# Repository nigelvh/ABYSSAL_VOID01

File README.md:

# ABYSSAL.NETWORK VOID01
A routing & switching learning platform built around the Raspberry Pi Compute Module 4, and the Microchip KSZ9477 gigabit ethernet switch.

## Hardware
These are the hardware design files. They're almost certainly terrible. Replicate this device at your own peril.

## Software
The Raspberry Pi Compute Module is installed with standard Raspbian. Configuration of the switching functions of the KSZ9477 are done via scripts communicating via the SPI bus. Configuration of routing functions are as per standard Linux methods.

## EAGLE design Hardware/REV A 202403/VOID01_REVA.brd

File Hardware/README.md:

# ABYSSAL.NETWORK VOID01 Hardware
This is a custom routing and switching learning platform based on the Raspberry Pi Compute Module 4 and the Microchip KSZ9477 gigabit ethernet switch.

The RPi provides for a standard linux platform to enable easy development, with simple scripting to configure the KSZ9477, and linux routing functions. This provides a lower barrier to entry learning platform, as compared to an embedded processor of some sort.

A CM4 Lite module is chosen, utilizing SD card based storage to simplify installation of the RPi OS.

A USB serial interface is provided to allow access to the RPi Serial Console, allowing for non-network based access/recovery.

The KSZ9477 switch is an inexpensive off-the-shelf switching chip, with a relatively rich feature set. Providing 5 PHY interfaces (4 ethernet jacks, and 1 connected to the onboard RPi), 1 RGMII interface (not used), and 1 SGMII interface (SFP Port).

A standard center-positive barrel jack accepts nominal 12V DC power. The input range should be roughly 8-26V. Onboard regulation generates 5V, 3.3V, 2.5V, and 1.2V rails necessary for the RPi and KSZ9477.

## REV A 202403
The first revision of the board. Designed in March 2024.

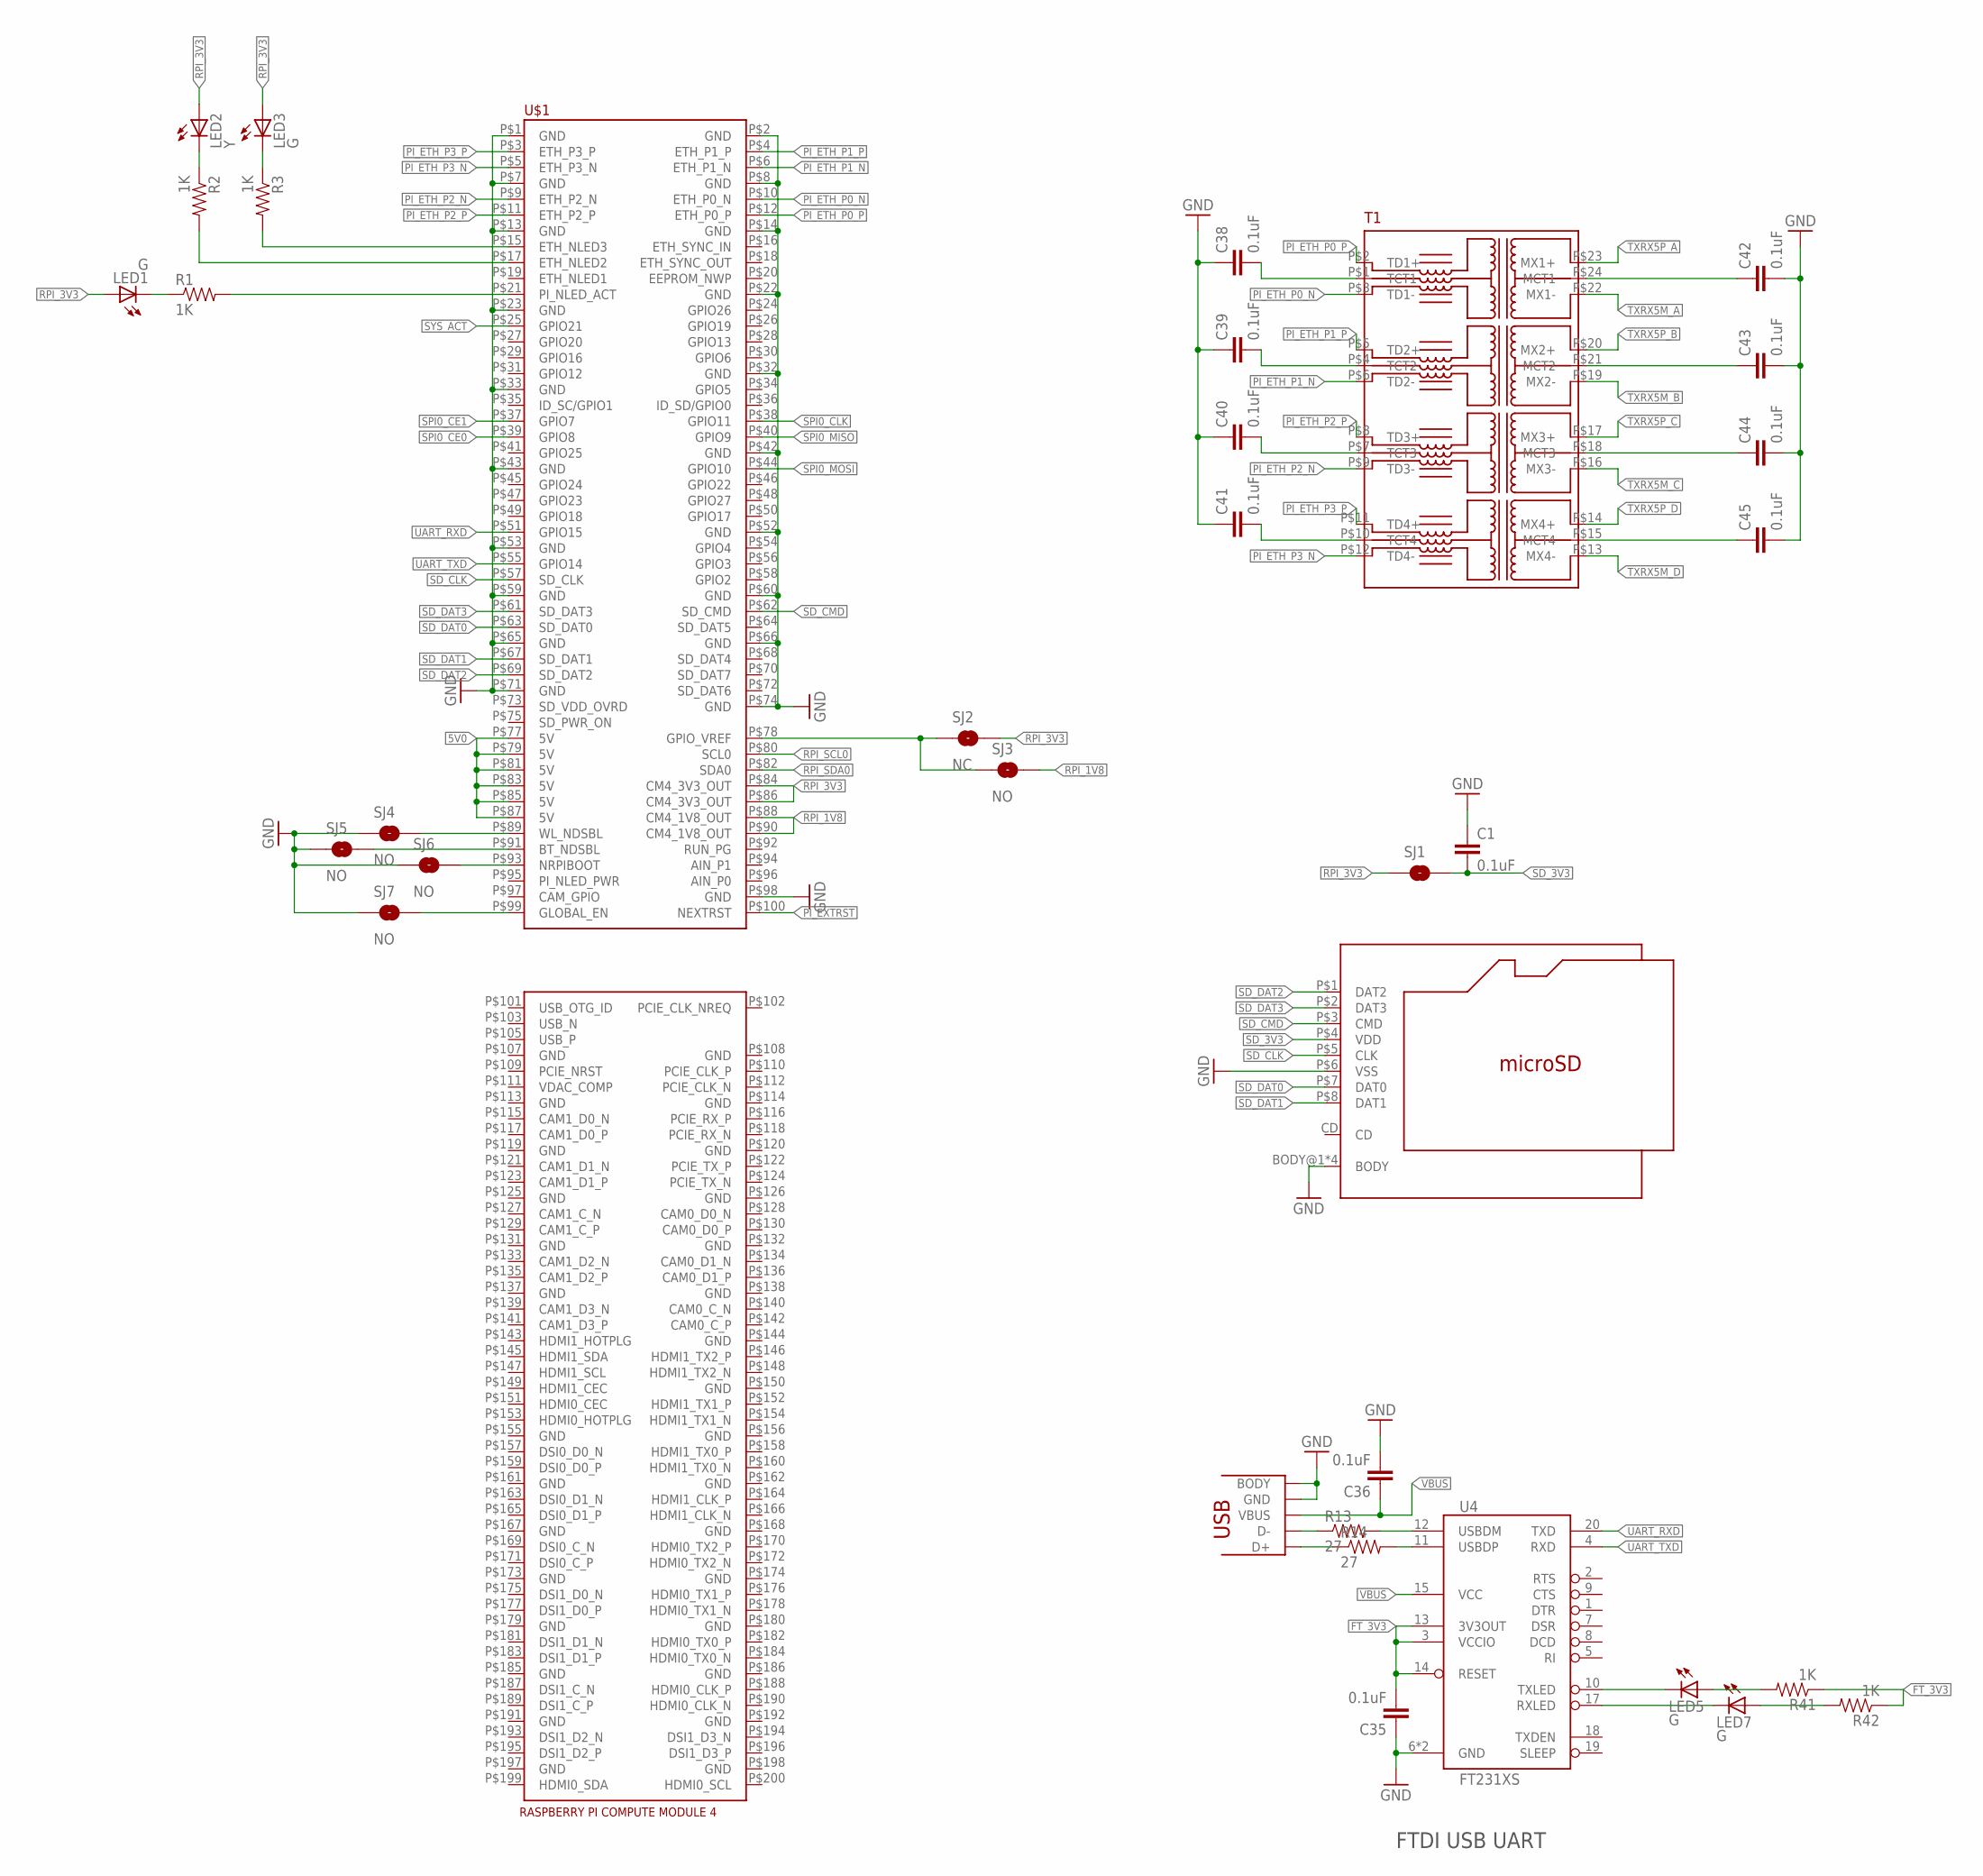
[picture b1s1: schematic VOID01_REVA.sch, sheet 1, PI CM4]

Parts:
C1, C35, C36, C38, C39, C40, C41, C42, C43, C44, C45: 0.1uF; 0603-CAP
J1: MICROSD; MSD-4-A
LED1, LED3, LED5, LED7: G; LED-0603
LED2: Y; LED-0603
R1, R2, R3: 1K; 0402-RES
R13, R14: 27; 0603-RES
R41, R42: 1K; 0603-RES
SJ1: SOLDERJUMPERTRACE; SJ_2S-TRACE
SJ2: NC; SJ_2S-TRACE
SJ3, SJ4, SJ5, SJ6, SJ7: NO; SJ_2S-NO
T1: HX6098NL
U4: FT231XS; SSOP-20
U$1: RPI-CM4
U$2: USB-MICROB; USB-MICROB-10118192

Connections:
5V0: U$1.P$77 (5V), U$1.P$79 (5V), U$1.P$81 (5V), U$1.P$83 (5V), U$1.P$85 (5V), U$1.P$87 (5V); also elsewhere on the board
FT_3V3: C35.2, R41.1, R42.1, U4.3 (VCCIO), U4.13 (3V3OUT), U4.14 (RESET)
GND: C1.1, C35.1, C36.2, C38.1, C39.1, C40.1, C41.1, C42.2, C43.2, C44.2, C45.2, J1.BODY@1 (BODY), J1.BODY@2 (BODY), J1.BODY@3 (BODY), J1.BODY@4 (BODY), J1.P$6 (VSS), SJ4.1, SJ5.1, SJ6.1, SJ7.1, U4.6 (GND), U4.16 (GND), U$1.P$1 (GND), U$1.P$2 (GND), U$1.P$7 (GND), U$1.P$8 (GND), U$1.P$13 (GND), U$1.P$14 (GND), U$1.P$22 (GND), U$1.P$23 (GND), U$1.P$32 (GND), U$1.P$33 (GND), U$1.P$42 (GND), U$1.P$43 (GND), U$1.P$52 (GND), U$1.P$53 (GND), U$1.P$59 (GND), U$1.P$60 (GND), U$1.P$65 (GND), U$1.P$66 (GND), U$1.P$71 (GND), U$1.P$74 (GND), U$1.P$98 (GND), U$2.5 (GND), U$2.BODY@1 (BODY), U$2.BODY@2 (BODY), U$2.BODY@3 (BODY), U$2.BODY@4 (BODY), U$2.BODY@5 (BODY), U$2.BODY@6 (BODY); also elsewhere on the board
unnamed: SJ2.1, SJ3.1, U$1.P$78 (GPIO_VREF)
unnamed: SJ4.2, U$1.P$89 (WL_NDSBL)
unnamed: SJ5.2, U$1.P$91 (BT_NDSBL)
unnamed: LED2.C, R2.1
unnamed: SJ6.2, U$1.P$93 (NRPIBOOT)
unnamed: R1.2, U$1.P$21 (PI_NLED_ACT)
unnamed: LED1.C, R1.1
unnamed: LED3.C, R3.1
unnamed: R2.2, U$1.P$17 (ETH_NLED2)
unnamed: R3.2, U$1.P$15 (ETH_NLED3)
unnamed: SJ7.2, U$1.P$99 (GLOBAL_EN)
unnamed: R13.1, U$2.2 (D-)
unnamed: R14.1, U$2.3 (D+)
unnamed: R14.2, U4.11 (USBDP)
unnamed: R13.2, U4.12 (USBDM)
unnamed: C38.2, T1.P$1 (TCT1)
unnamed: C39.2, T1.P$4 (TCT2)
unnamed: C40.2, T1.P$7 (TCT3)
unnamed: C41.2, T1.P$10 (TCT4)
unnamed: C45.1, T1.P$15 (MCT4)
unnamed: C44.1, T1.P$18 (MCT3)
unnamed: C43.1, T1.P$21 (MCT2)
unnamed: C42.1, T1.P$24 (MCT1)
unnamed: LED5.C, U4.10 (TXLED)
unnamed: LED5.A, R41.2
unnamed: LED7.C, U4.17 (RXLED)
unnamed: LED7.A, R42.2
PI_ETH_P0_N: T1.P$3 (TD1-), U$1.P$10 (ETH_P0_N)
PI_ETH_P0_P: T1.P$2 (TD1+), U$1.P$12 (ETH_P0_P)
PI_ETH_P1_N: T1.P$6 (TD2-), U$1.P$6 (ETH_P1_N)
PI_ETH_P1_P: T1.P$5 (TD2+), U$1.P$4 (ETH_P1_P)
PI_ETH_P2_N: T1.P$9 (TD3-), U$1.P$9 (ETH_P2_N)
PI_ETH_P2_P: T1.P$8 (TD3+), U$1.P$11 (ETH_P2_P)
PI_ETH_P3_N: T1.P$12 (TD4-), U$1.P$5 (ETH_P3_N)
PI_ETH_P3_P: T1.P$11 (TD4+), U$1.P$3 (ETH_P3_P)
PI_EXTRST: U$1.P$100 (NEXTRST); also elsewhere on the board
RPI_1V8: SJ3.2, U$1.P$88 (CM4_1V8_OUT), U$1.P$90 (CM4_1V8_OUT)
RPI_3V3: LED1.A, LED2.A, LED3.A, SJ1.1, SJ2.2, U$1.P$84 (CM4_3V3_OUT), U$1.P$86 (CM4_3V3_OUT)
RPI_SCL0: U$1.P$80 (SCL0); also elsewhere on the board
RPI_SDA0: U$1.P$82 (SDA0); also elsewhere on the board
SD_3V3: C1.2, J1.P$4 (VDD), SJ1.2
SD_CLK: J1.P$5 (CLK), U$1.P$57 (SD_CLK)
SD_CMD: J1.P$3 (CMD), U$1.P$62 (SD_CMD)
SD_DAT0: J1.P$7 (DAT0), U$1.P$63 (SD_DAT0)
SD_DAT1: J1.P$8 (DAT1), U$1.P$67 (SD_DAT1)
SD_DAT2: J1.P$1 (DAT2), U$1.P$69 (SD_DAT2)
SD_DAT3: J1.P$2 (DAT3), U$1.P$61 (SD_DAT3)
SPI0_CE0: U$1.P$39 (GPIO8); also elsewhere on the board
SPI0_CE1: U$1.P$37 (GPIO7)
SPI0_CLK: U$1.P$38 (GPIO11); also elsewhere on the board
SPI0_MISO: U$1.P$40 (GPIO9); also elsewhere on the board
SPI0_MOSI: U$1.P$44 (GPIO10); also elsewhere on the board
SYS_ACT: U$1.P$25 (GPIO21); also elsewhere on the board
TXRX5M_A: T1.P$22 (MX1-); also elsewhere on the board
TXRX5M_B: T1.P$19 (MX2-); also elsewhere on the board
TXRX5M_C: T1.P$16 (MX3-); also elsewhere on the board
TXRX5M_D: T1.P$13 (MX4-); also elsewhere on the board
TXRX5P_A: T1.P$23 (MX1+); also elsewhere on the board
TXRX5P_B: T1.P$20 (MX2+); also elsewhere on the board
TXRX5P_C: T1.P$17 (MX3+); also elsewhere on the board
TXRX5P_D: T1.P$14 (MX4+); also elsewhere on the board
UART_RXD: U4.20 (TXD), U$1.P$51 (GPIO15)
UART_TXD: U4.4 (RXD), U$1.P$55 (GPIO14)
VBUS: C36.1, U4.15 (VCC), U$2.1 (VBUS)

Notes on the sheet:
FTDI USB UART

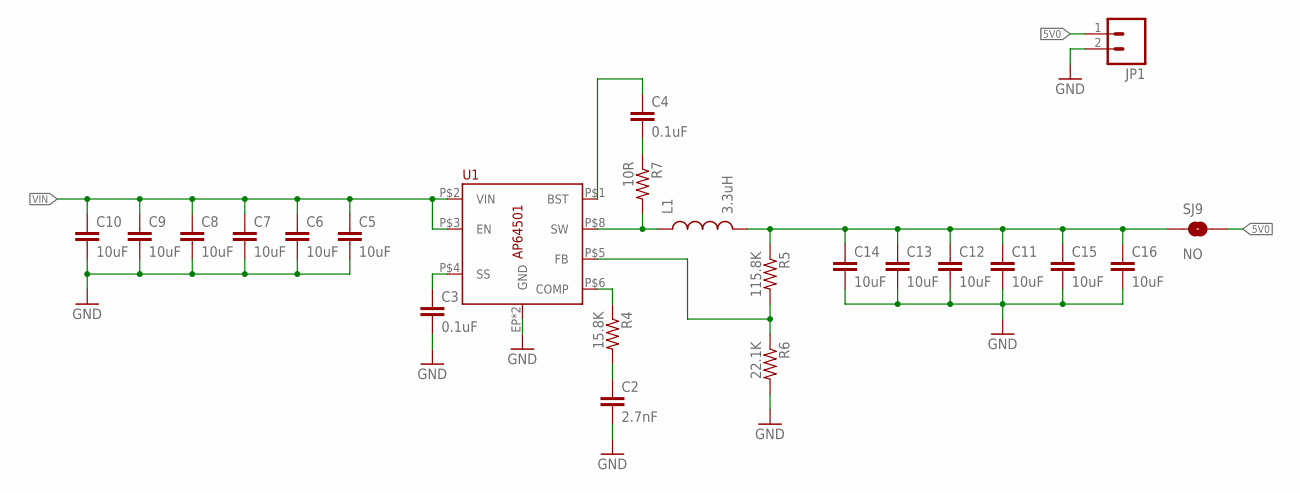
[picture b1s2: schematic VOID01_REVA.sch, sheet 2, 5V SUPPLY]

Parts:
C2: 2.7nF; 0603-CAP
C3, C4: 0.1uF; 0603-CAP
C5, C6, C7, C8, C9, C10, C11, C12, C13, C14, C15, C16: 10uF; 1206
JP1: M02PTH3; 1X02_LONGPADS
L1: 3.3uH; SRN6045TA
R4: 15.8K; 0603-RES
R5: 115.8K; 0603-RES
R6: 22.1K; 0603-RES
R7: 10R; 0603-RES
SJ9: NO; SJ_2S-NO
U1: AP64501; SO-8EP

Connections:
5V0: JP1.1, SJ9.2; also elsewhere on the board
GND: C2.2, C3.2, C5.2, C6.2, C7.2, C8.2, C9.2, C10.2, C11.2, C12.2, C13.2, C14.2, C15.2, C16.2, JP1.2, R6.2, U1.EP (GND), U1.P$7 (GND); also elsewhere on the board
unnamed: C3.1, U1.P$4 (SS)
unnamed: R4.1, U1.P$6 (COMP)
unnamed: C2.1, R4.2
unnamed: R5.2, R6.1, U1.P$5 (FB)
unnamed: L1.P$1 (1), R7.2, U1.P$8 (SW)
unnamed: C4.2, R7.1
unnamed: C4.1, U1.P$1 (BST)
unnamed: C11.1, C12.1, C13.1, C14.1, C15.1, C16.1, L1.P$2 (2), R5.1, SJ9.1
VIN: C5.1, C6.1, C7.1, C8.1, C9.1, C10.1, U1.P$2 (VIN), U1.P$3 (EN); also elsewhere on the board

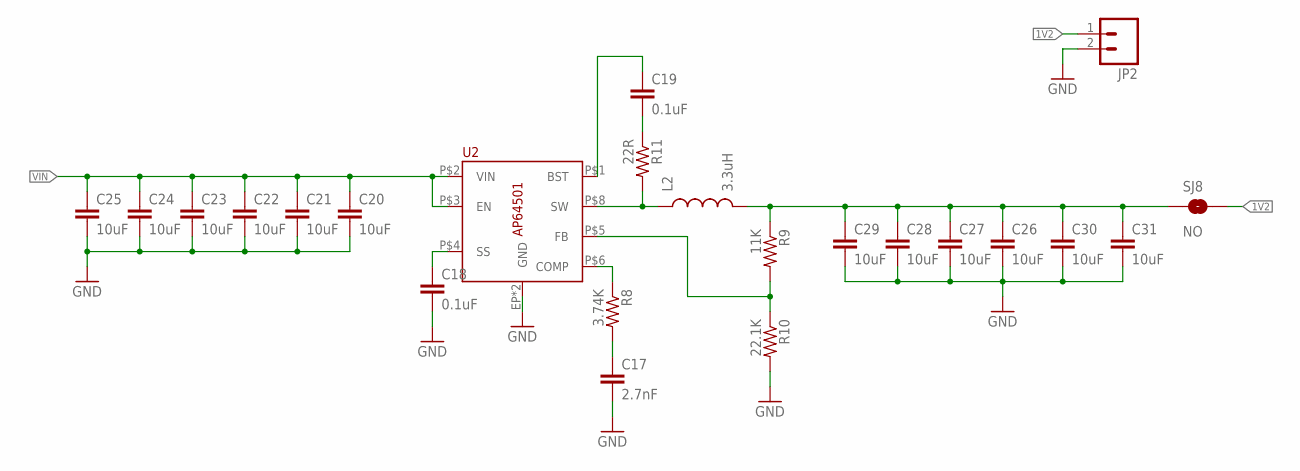
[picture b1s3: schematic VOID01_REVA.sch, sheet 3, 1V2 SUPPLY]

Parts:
C17: 2.7nF; 0603-CAP
C18, C19: 0.1uF; 0603-CAP
C20, C21, C22, C23, C24, C25, C26, C27, C28, C29, C30, C31: 10uF; 1206
JP2: M02PTH3; 1X02_LONGPADS
L2: 3.3uH; SRN6045TA
R8: 3.74K; 0603-RES
R9: 11K; 0603-RES
R10: 22.1K; 0603-RES
R11: 22R; 0603-RES
SJ8: NO; SJ_2S-NO
U2: AP64501; SO-8EP

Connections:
1V2: JP2.1, SJ8.2; also elsewhere on the board
GND: C17.2, C18.2, C20.2, C21.2, C22.2, C23.2, C24.2, C25.2, C26.2, C27.2, C28.2, C29.2, C30.2, C31.2, JP2.2, R10.2, U2.EP (GND), U2.P$7 (GND); also elsewhere on the board
unnamed: C18.1, U2.P$4 (SS)
unnamed: R8.1, U2.P$6 (COMP)
unnamed: C17.1, R8.2
unnamed: R9.2, R10.1, U2.P$5 (FB)
unnamed: L2.P$1 (1), R11.2, U2.P$8 (SW)
unnamed: C19.2, R11.1
unnamed: C19.1, U2.P$1 (BST)
unnamed: C26.1, C27.1, C28.1, C29.1, C30.1, C31.1, L2.P$2 (2), R9.1, SJ8.1
VIN: C20.1, C21.1, C22.1, C23.1, C24.1, C25.1, U2.P$2 (VIN), U2.P$3 (EN); also elsewhere on the board

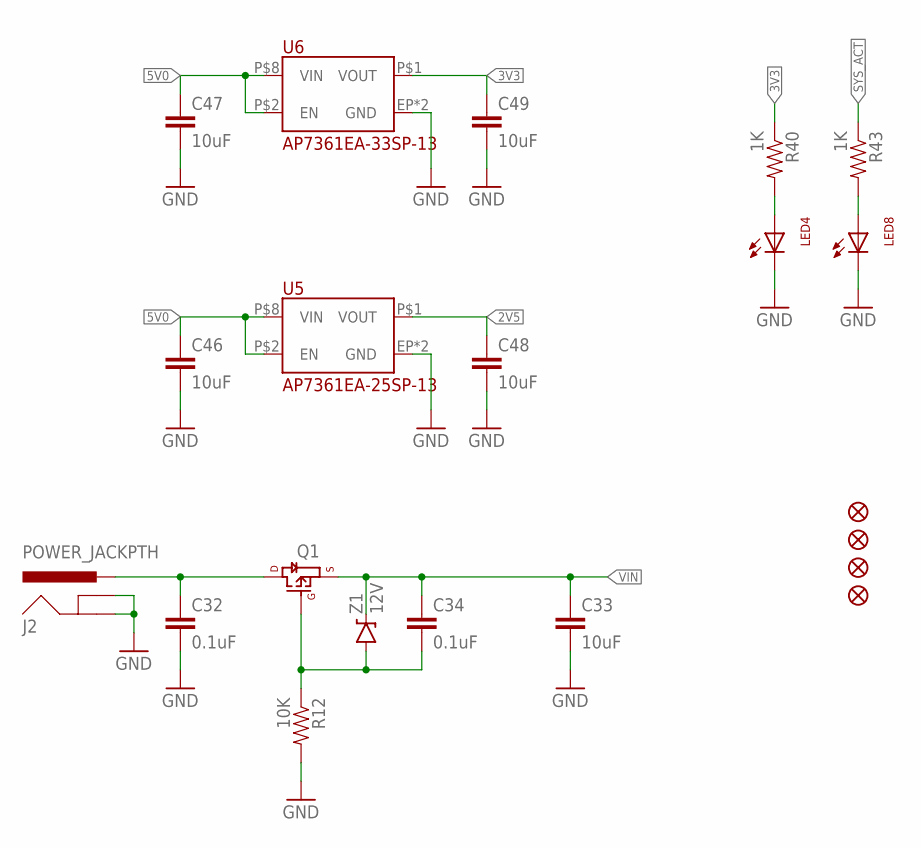
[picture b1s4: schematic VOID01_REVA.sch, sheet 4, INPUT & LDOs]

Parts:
C32, C34: 0.1uF; 0603-CAP
C33, C46, C47, C48, C49: 10uF; 1206
FID1, FID2, FID3, FID4: FIDUCIAL
J2: POWER_JACKPTH; POWER_JACK_PTH
LED4, LED8: LED; LED_QBL7XX80D-MP4A
Q1: MOSFET_P_CHANNELDMP4015SSS; SO08
R12: 10K; 0603-RES
R40, R43: 1K; 0603-RES
U5: AP7361EA-25SP-13; SO-8EP
U6: AP7361EA-33SP-13; SO-8EP
Z1: 12V; SOT-23

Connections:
2V5: C48.1, U5.P$1 (VOUT); also elsewhere on the board
3V3: C49.1, R40.1, U6.P$1 (VOUT); also elsewhere on the board
5V0: C46.1, C47.1, U5.P$2 (EN), U5.P$8 (VIN), U6.P$2 (EN), U6.P$8 (VIN); also elsewhere on the board
GND: C32.2, C33.2, C46.2, C47.2, C48.2, C49.2, J2.GND, J2.GNDBREAK, LED4.C, LED8.C, R12.2, U5.EP (GND), U5.P$4 (GND), U6.EP (GND), U6.P$4 (GND); also elsewhere on the board
unnamed: C32.1, J2.PWR, Q1.5 (D), Q1.6 (D), Q1.7 (D), Q1.8 (D)
unnamed: C34.2, Q1.4 (G), R12.1, Z1.1 (A)
unnamed: LED8.A, R43.2
unnamed: LED4.A, R40.2
SYS_ACT: R43.1; also elsewhere on the board
VIN: C33.1, C34.1, Q1.1 (S), Q1.2 (S), Q1.3 (S), Z1.3 (C); also elsewhere on the board

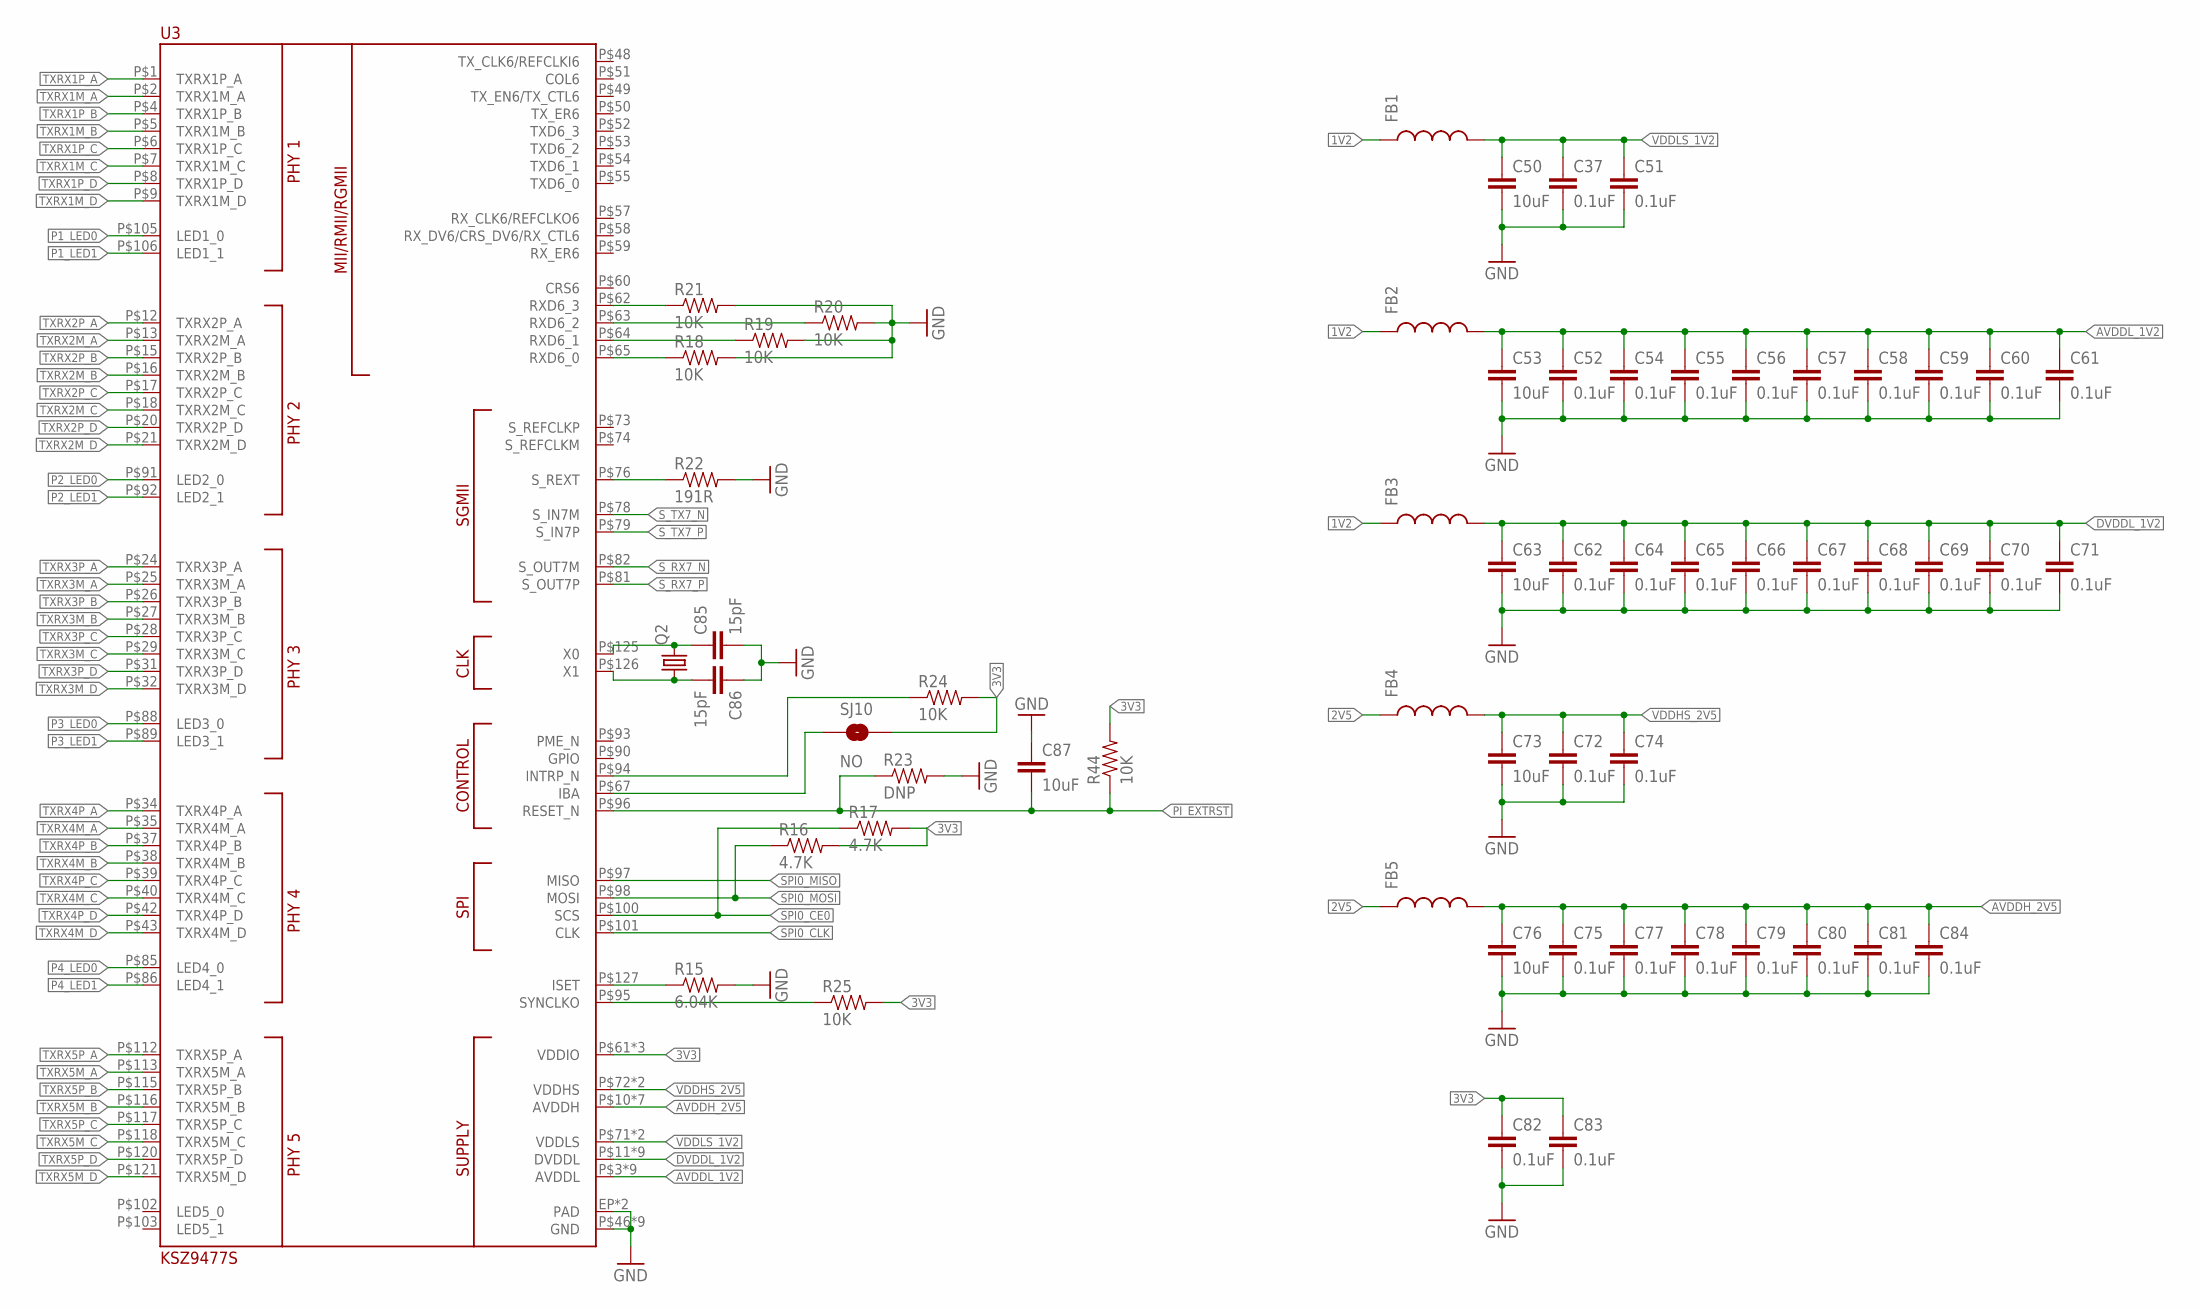
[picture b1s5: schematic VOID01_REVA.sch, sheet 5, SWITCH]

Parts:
C37, C51, C52, C54, C55, C56, C57, C58, C59, C60, C61, C62, C64, C65, C66, C67, C68, C69, C70, C71, C72, C74, C75, C77, C78, C79, C80, C81, C82, C83, C84: 0.1uF; 0402-CAP
C50, C53, C63, C73, C76, C87: 10uF; 1206
C85, C86: 15pF; 0402-CAP
FB1, FB2, FB3, FB4, FB5: INDUCTOR0805; 0805
Q2: CRYSTAL3.2X2.5; CRYSTAL_3.2X2.5
R15: 6.04K; 0402-RES
R16, R17: 4.7K; 0402-RES
R18, R19, R20, R21, R24, R25, R44: 10K; 0402-RES
R22: 191R; 0402-RES
R23: DNP; 0402-RES
SJ10: NO; SJ_2S-NO
U3: KSZ9477S; TQFP-128-EP

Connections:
1V2: FB1.1, FB2.1, FB3.1; also elsewhere on the board
2V5: FB4.1, FB5.1; also elsewhere on the board
3V3: C82.1, C83.1, R16.2, R17.2, R24.2, R25.2, R44.2, SJ10.2, U3.P$61 (VDDIO), U3.P$68 (VDDIO), U3.P$99 (VDDIO); also elsewhere on the board
AVDDH_2V5: C75.1, C76.1, C77.1, C78.1, C79.1, C80.1, C81.1, C84.1, FB5.2, U3.P$10 (AVDDH), U3.P$22 (AVDDH), U3.P$33 (AVDDH), U3.P$44 (AVDDH), U3.P$111 (AVDDH), U3.P$122 (AVDDH), U3.P$128 (AVDDH)
AVDDL_1V2: C52.1, C53.1, C54.1, C55.1, C56.1, C57.1, C58.1, C59.1, C60.1, C61.1, FB2.2, U3.P$3 (AVDDL), U3.P$14 (AVDDL), U3.P$19 (AVDDL), U3.P$30 (AVDDL), U3.P$36 (AVDDL), U3.P$41 (AVDDL), U3.P$114 (AVDDL), U3.P$119 (AVDDL), U3.P$124 (AVDDL)
DVDDL_1V2: C62.1, C63.1, C64.1, C65.1, C66.1, C67.1, C68.1, C69.1, C70.1, C71.1, FB3.2, U3.P$11 (DVDDL), U3.P$23 (DVDDL), U3.P$45 (DVDDL), U3.P$56 (DVDDL), U3.P$66 (DVDDL), U3.P$70 (DVDDL), U3.P$87 (DVDDL), U3.P$104 (DVDDL), U3.P$110 (DVDDL)
GND: C37.2, C50.2, C51.2, C52.2, C53.2, C54.2, C55.2, C56.2, C57.2, C58.2, C59.2, C60.2, C61.2, C62.2, C63.2, C64.2, C65.2, C66.2, C67.2, C68.2, C69.2, C70.2, C71.2, C72.2, C73.2, C74.2, C75.2, C76.2, C77.2, C78.2, C79.2, C80.2, C81.2, C82.2, C83.2, C84.2, C85.2, C86.1, C87.1, R15.2, R18.2, R19.2, R20.2, R21.2, R22.2, R23.2, U3.EP (PAD), U3.EP1 (PAD), U3.P$46 (GND), U3.P$47 (GND), U3.P$69 (GND), U3.P$75 (GND), U3.P$77 (GND), U3.P$80 (GND), U3.P$107 (GND), U3.P$109 (GND), U3.P$123 (GND); also elsewhere on the board
unnamed: R15.1, U3.P$127 (ISET)
unnamed: R21.1, U3.P$62 (RXD6_3)
unnamed: R20.1, U3.P$63 (RXD6_2)
unnamed: R19.1, U3.P$64 (RXD6_1)
unnamed: R18.1, U3.P$65 (RXD6_0)
unnamed: R22.1, U3.P$76 (S_REXT)
unnamed: R25.1, U3.P$95 (SYNCLKO)
unnamed: R24.1, U3.P$94 (INTRP_N)
unnamed: SJ10.1, U3.P$67 (IBA)
unnamed: C86.2, Q2.P$1 (1), U3.P$126 (X1)
unnamed: C85.1, Q2.P$3 (2), U3.P$125 (X0)
P1_LED0: U3.P$105 (LED1_0); also elsewhere on the board
P1_LED1: U3.P$106 (LED1_1); also elsewhere on the board
P2_LED0: U3.P$91 (LED2_0); also elsewhere on the board
P2_LED1: U3.P$92 (LED2_1); also elsewhere on the board
P3_LED0: U3.P$88 (LED3_0); also elsewhere on the board
P3_LED1: U3.P$89 (LED3_1); also elsewhere on the board
P4_LED0: U3.P$85 (LED4_0); also elsewhere on the board
P4_LED1: U3.P$86 (LED4_1); also elsewhere on the board
PI_EXTRST: C87.2, R23.1, R44.1, U3.P$96 (RESET_N); also elsewhere on the board
SPI0_CE0: R17.1, U3.P$100 (SCS); also elsewhere on the board
SPI0_CLK: U3.P$101 (CLK); also elsewhere on the board
SPI0_MISO: U3.P$97 (MISO); also elsewhere on the board
SPI0_MOSI: R16.1, U3.P$98 (MOSI); also elsewhere on the board
S_RX7_N: U3.P$82 (S_OUT7M); also elsewhere on the board
S_RX7_P: U3.P$81 (S_OUT7P); also elsewhere on the board
S_TX7_N: U3.P$78 (S_IN7M); also elsewhere on the board
S_TX7_P: U3.P$79 (S_IN7P); also elsewhere on the board
TXRX1M_A: U3.P$2 (TXRX1M_A); also elsewhere on the board
TXRX1M_B: U3.P$5 (TXRX1M_B); also elsewhere on the board
TXRX1M_C: U3.P$7 (TXRX1M_C); also elsewhere on the board
TXRX1M_D: U3.P$9 (TXRX1M_D); also elsewhere on the board
TXRX1P_A: U3.P$1 (TXRX1P_A); also elsewhere on the board
TXRX1P_B: U3.P$4 (TXRX1P_B); also elsewhere on the board
TXRX1P_C: U3.P$6 (TXRX1P_C); also elsewhere on the board
TXRX1P_D: U3.P$8 (TXRX1P_D); also elsewhere on the board
TXRX2M_A: U3.P$13 (TXRX2M_A); also elsewhere on the board
TXRX2M_B: U3.P$16 (TXRX2M_B); also elsewhere on the board
TXRX2M_C: U3.P$18 (TXRX2M_C); also elsewhere on the board
TXRX2M_D: U3.P$21 (TXRX2M_D); also elsewhere on the board
TXRX2P_A: U3.P$12 (TXRX2P_A); also elsewhere on the board
TXRX2P_B: U3.P$15 (TXRX2P_B); also elsewhere on the board
TXRX2P_C: U3.P$17 (TXRX2P_C); also elsewhere on the board
TXRX2P_D: U3.P$20 (TXRX2P_D); also elsewhere on the board
TXRX3M_A: U3.P$25 (TXRX3M_A); also elsewhere on the board
TXRX3M_B: U3.P$27 (TXRX3M_B); also elsewhere on the board
TXRX3M_C: U3.P$29 (TXRX3M_C); also elsewhere on the board
TXRX3M_D: U3.P$32 (TXRX3M_D); also elsewhere on the board
TXRX3P_A: U3.P$24 (TXRX3P_A); also elsewhere on the board
TXRX3P_B: U3.P$26 (TXRX3P_B); also elsewhere on the board
TXRX3P_C: U3.P$28 (TXRX3P_C); also elsewhere on the board
TXRX3P_D: U3.P$31 (TXRX3P_D); also elsewhere on the board
TXRX4M_A: U3.P$35 (TXRX4M_A); also elsewhere on the board
TXRX4M_B: U3.P$38 (TXRX4M_B); also elsewhere on the board
TXRX4M_C: U3.P$40 (TXRX4M_C); also elsewhere on the board
TXRX4M_D: U3.P$43 (TXRX4M_D); also elsewhere on the board
TXRX4P_A: U3.P$34 (TXRX4P_A); also elsewhere on the board
TXRX4P_B: U3.P$37 (TXRX4P_B); also elsewhere on the board
TXRX4P_C: U3.P$39 (TXRX4P_C); also elsewhere on the board
TXRX4P_D: U3.P$42 (TXRX4P_D); also elsewhere on the board
TXRX5M_A: U3.P$113 (TXRX5M_A); also elsewhere on the board
TXRX5M_B: U3.P$116 (TXRX5M_B); also elsewhere on the board
TXRX5M_C: U3.P$118 (TXRX5M_C); also elsewhere on the board
TXRX5M_D: U3.P$121 (TXRX5M_D); also elsewhere on the board
TXRX5P_A: U3.P$112 (TXRX5P_A); also elsewhere on the board
TXRX5P_B: U3.P$115 (TXRX5P_B); also elsewhere on the board
TXRX5P_C: U3.P$117 (TXRX5P_C); also elsewhere on the board
TXRX5P_D: U3.P$120 (TXRX5P_D); also elsewhere on the board
VDDHS_2V5: C72.1, C73.1, C74.1, FB4.2, U3.P$72 (VDDHS), U3.P$83 (VDDHS)
VDDLS_1V2: C37.1, C50.1, C51.1, FB1.2, U3.P$71 (VDDLS), U3.P$84 (VDDLS)

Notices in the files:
parts and their libraries:
SparkFun: Licensing: CC v3.0 Share-Alike You are welcome to use this library for commercial purposes.
